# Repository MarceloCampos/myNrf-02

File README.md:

# myNrf-02

NRF24L01 board c/ ATMEGA328 (Arduino) feita para uso c/ redes MySensors e IoT myNrf-02
mais detalhes em http://marcelocampos.cc/index.php/2022/03/13/nova-versao-placa-nrf24l01-arduino/

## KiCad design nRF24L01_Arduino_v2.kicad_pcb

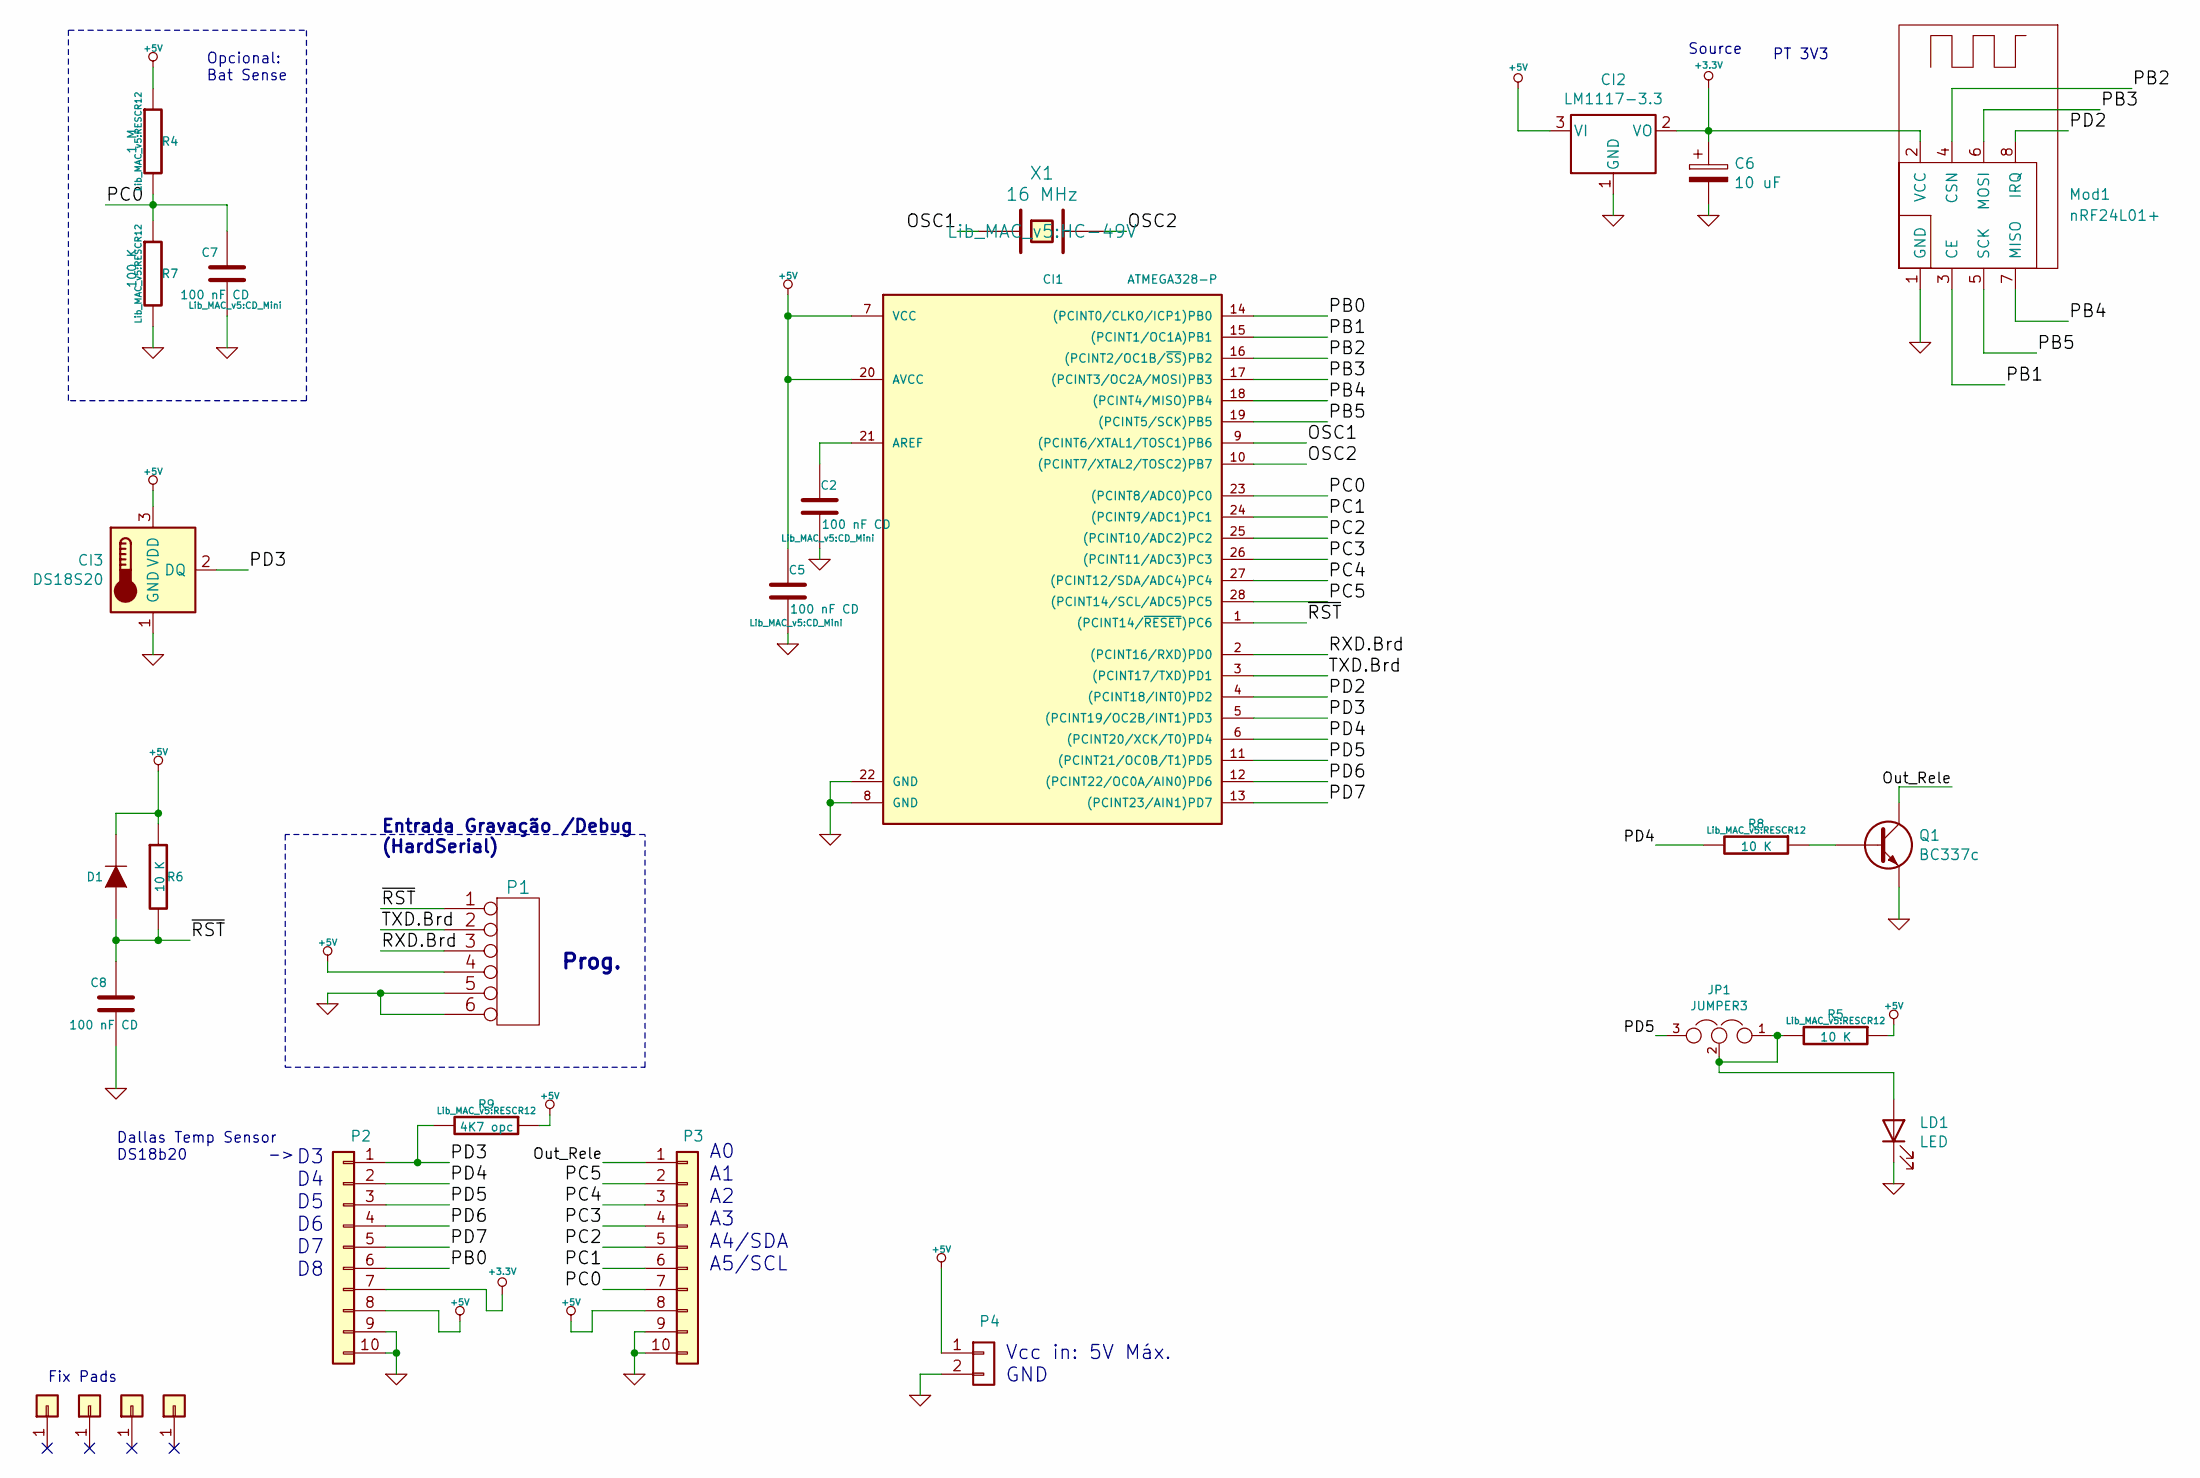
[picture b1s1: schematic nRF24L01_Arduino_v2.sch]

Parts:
C2, C5, C7, C8: 100 nF CD; CD_Mini
C6: 10 uF; CP_Radial_Tantal_D4.5mm_P2.50mm
CI1: ATMEGA328-P; DIP-28_W7.62mm_Socket
CI2: LM1117-3.3; SOT-223-3_TabPin2
CI3: DS18S20; TO-92_Inline
D1: 1N4148; DO-41
J3, J4, J5, J6: Conn_01x01; 1PAD
JP1: JUMPER3; SolderJumper-3_P1.3mm_Open_RoundedPad1.0x1.5mm
LD1: LED; LED_D3.0mm
Mod1: nRF24L01+; PinHeader_2x04_P2.54mm_Vertical
P1: CONN_6; CON6ICSP
P2, P3: Conn_01x10; PinHeader_1x10_P2.54mm_Vertical
P4: Conn_01x02; PinHeader_1x02_P2.54mm_Vertical
Q1: BC337c; TO-92_Inline
R4: 1 M; RESCR12
R5, R6, R8: 10 K; RESCR12
R7: 100 K; RESCR12
R9: 4K7 opc; RESCR12
X1: 16 MHz; HC-49V

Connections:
+3.3V: C6.1, CI2.2 (VO), Mod1.2 (VCC), P2.7
+5V: C5.1, CI1.7 (VCC), CI1.20 (AVCC), CI2.3 (VI), CI3.3 (VDD), D1.2 (K), P1.4, P2.8, P3.8, P4.1, R4.1, R5.1, R6.1, R9.1
/OSC1: CI1.9 ((PCINT6/XTAL1/TOSC1)PB6), X1.1
/OSC2: CI1.10 ((PCINT7/XTAL2/TOSC2)PB7), X1.2
/Out_Rele: P3.1, Q1.1 (C)
/PB0: CI1.14 ((PCINT0/CLKO/ICP1)PB0), P2.6
/PB1: CI1.15 ((PCINT1/OC1A)PB1), Mod1.3 (CE)
/PB2: CI1.16 ((PCINT2/OC1B/~SS~)PB2), Mod1.4 (CSN)
/PB3: CI1.17 ((PCINT3/OC2A/MOSI)PB3), Mod1.6 (MOSI)
/PB4: CI1.18 ((PCINT4/MISO)PB4), Mod1.7 (MISO)
/PB5: CI1.19 ((PCINT5/SCK)PB5), Mod1.5 (SCK)
/PC0: C7.1, CI1.23 ((PCINT8/ADC0)PC0), P3.7, R4.2, R7.1
/PC1: CI1.24 ((PCINT9/ADC1)PC1), P3.6
/PC2: CI1.25 ((PCINT10/ADC2)PC2), P3.5
/PC3: CI1.26 ((PCINT11/ADC3)PC3), P3.4
/PC4: CI1.27 ((PCINT12/SDA/ADC4)PC4), P3.3
/PC5: CI1.28 ((PCINT14/SCL/ADC5)PC5), P3.2
/PD2: CI1.4 ((PCINT18/INT0)PD2), Mod1.8 (IRQ)
/PD3: CI1.5 ((PCINT19/OC2B/INT1)PD3), CI3.2 (DQ), P2.1, R9.2
/PD4: CI1.6 ((PCINT20/XCK/T0)PD4), P2.2, R8.2
/PD5: CI1.11 ((PCINT21/OC0B/T1)PD5), JP1.3, P2.3
/PD6: CI1.12 ((PCINT22/OC0A/AIN0)PD6), P2.4
/PD7: CI1.13 ((PCINT23/AIN1)PD7), P2.5
/RXD.Brd: CI1.2 ((PCINT16/RXD)PD0), P1.3
/TXD.Brd: CI1.3 ((PCINT17/TXD)PD1), P1.2
/~RST: C8.1, CI1.1 ((PCINT14/~RESET~)PC6), D1.1 (A), P1.1, R6.2
GND: C2.2, C5.2, C6.2, C7.2, C8.2, CI1.8 (GND), CI1.22 (GND), CI2.1 (GND), CI3.1 (GND), LD1.1 (K), Mod1.1 (GND), P1.5, P1.6, P2.9, P2.10, P3.9, P3.10, P4.2, Q1.3 (E), R7.2
unnamed: C2.1, CI1.21 (AREF)
unnamed: JP1.1, JP1.2, LD1.2 (A), R5.2
unnamed: Q1.2 (B), R8.1

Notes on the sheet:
Prog.
Entrada Gravação /Debug (HardSerial)
D3 D4 D5 D6 D7 D8
Vcc in: 5V Máx. GND
Fix Pads
Source
A0 A1 A2 A3 A4/SDA A5/SCL
PT 3V3
Opcional: Bat Sense
Dallas Temp Sensor DS18b20 ->

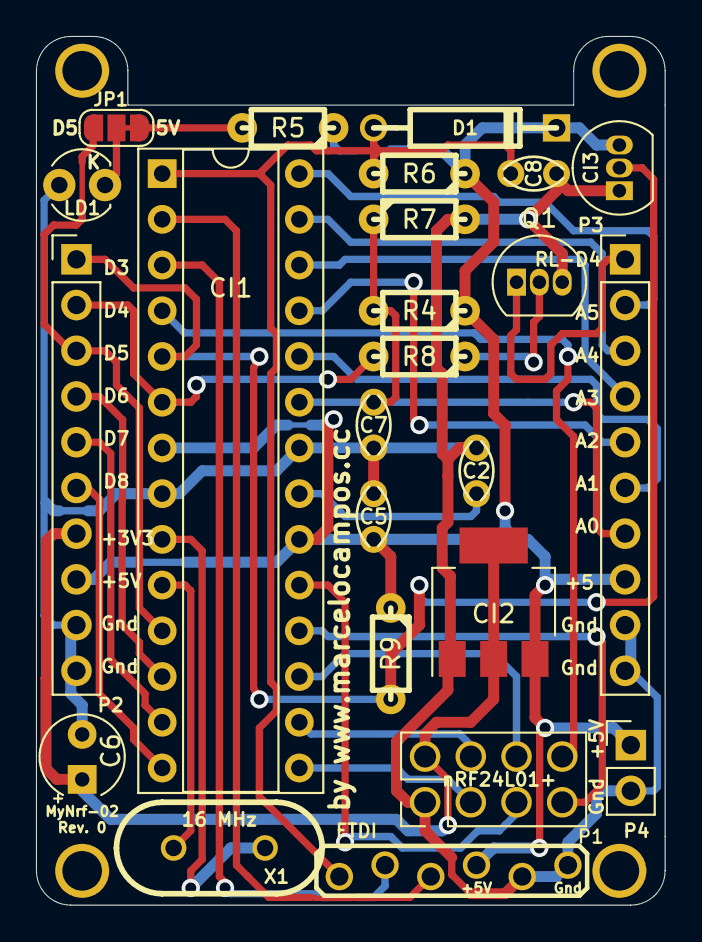
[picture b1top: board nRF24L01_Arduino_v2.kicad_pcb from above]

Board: 2 copper layers, 34.9 x 48.3 mm, 28 parts (0 on the bottom side), 30 nets.

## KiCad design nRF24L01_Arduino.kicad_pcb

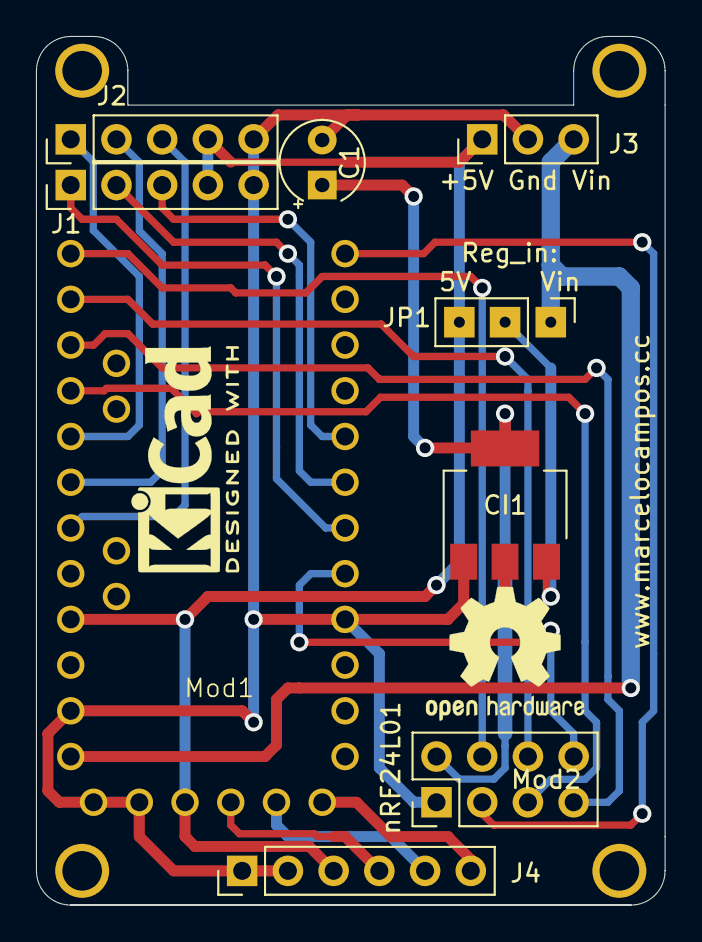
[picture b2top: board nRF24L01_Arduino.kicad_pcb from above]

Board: 2 copper layers, 34.9 x 48.3 mm, 13 parts (1 on the bottom side), 20 nets.

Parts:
C1: 10 uF; CP_Radial_Tantal_D4.5mm_P2.50mm
CI1: LM1117-3.3; SOT-223-3_TabPin2
J1, J2: Conn_01x05; PinHeader_1x05_P2.54mm_Vertical
J3: Conn_01x03; PinHeader_1x03_P2.54mm_Vertical
J4: Conn_01x06; PinHeader_1x06_P2.54mm_Vertical
J11, J12, J13, J14: Conn_01x01; 1PAD
JP1: Jumper_NC_Dual; PinHeader_1x03_P2.54mm_Vertical
Mod1: ARDUPROMINI; ArduProMini
Mod2: nRF24L01+; PinHeader_2x04_P2.54mm_Vertical

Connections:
/CE: Mod1.18, Mod2.3
/CSN-CS: Mod1.30, Mod2.4
/MISO: Mod1.28, Mod2.7
/MOSI: Mod1.29, Mod2.6
/SCK: Mod1.27, Mod2.5
/~IRQ: Mod1.11, Mod2.8
Earth: C1.2, CI1.1, J1.5, J2.5, J3.2, J4.1, J4.2, Mod1.1, Mod1.2, Mod1.10, Mod1.20, Mod2.1
unnamed: C1.1, CI1.2, Mod2.2
unnamed: CI1.3, JP1.2
unnamed: J1.1, Mod1.12
unnamed: J1.2, Mod1.13
unnamed: J1.3, Mod1.14
unnamed: J1.4, J2.4, J3.1, J4.3, JP1.3, Mod1.3, Mod1.22
unnamed: J2.1, Mod1.26
unnamed: J2.2, Mod1.25
unnamed: J2.3, Mod1.24
unnamed: J3.3, JP1.1, Mod1.19
unnamed: J4.4, Mod1.4
unnamed: J4.5, Mod1.5
unnamed: J4.6, Mod1.6

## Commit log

2022-03-13 init
2022-03-13 uploaded main files
2022-03-13 upload images
